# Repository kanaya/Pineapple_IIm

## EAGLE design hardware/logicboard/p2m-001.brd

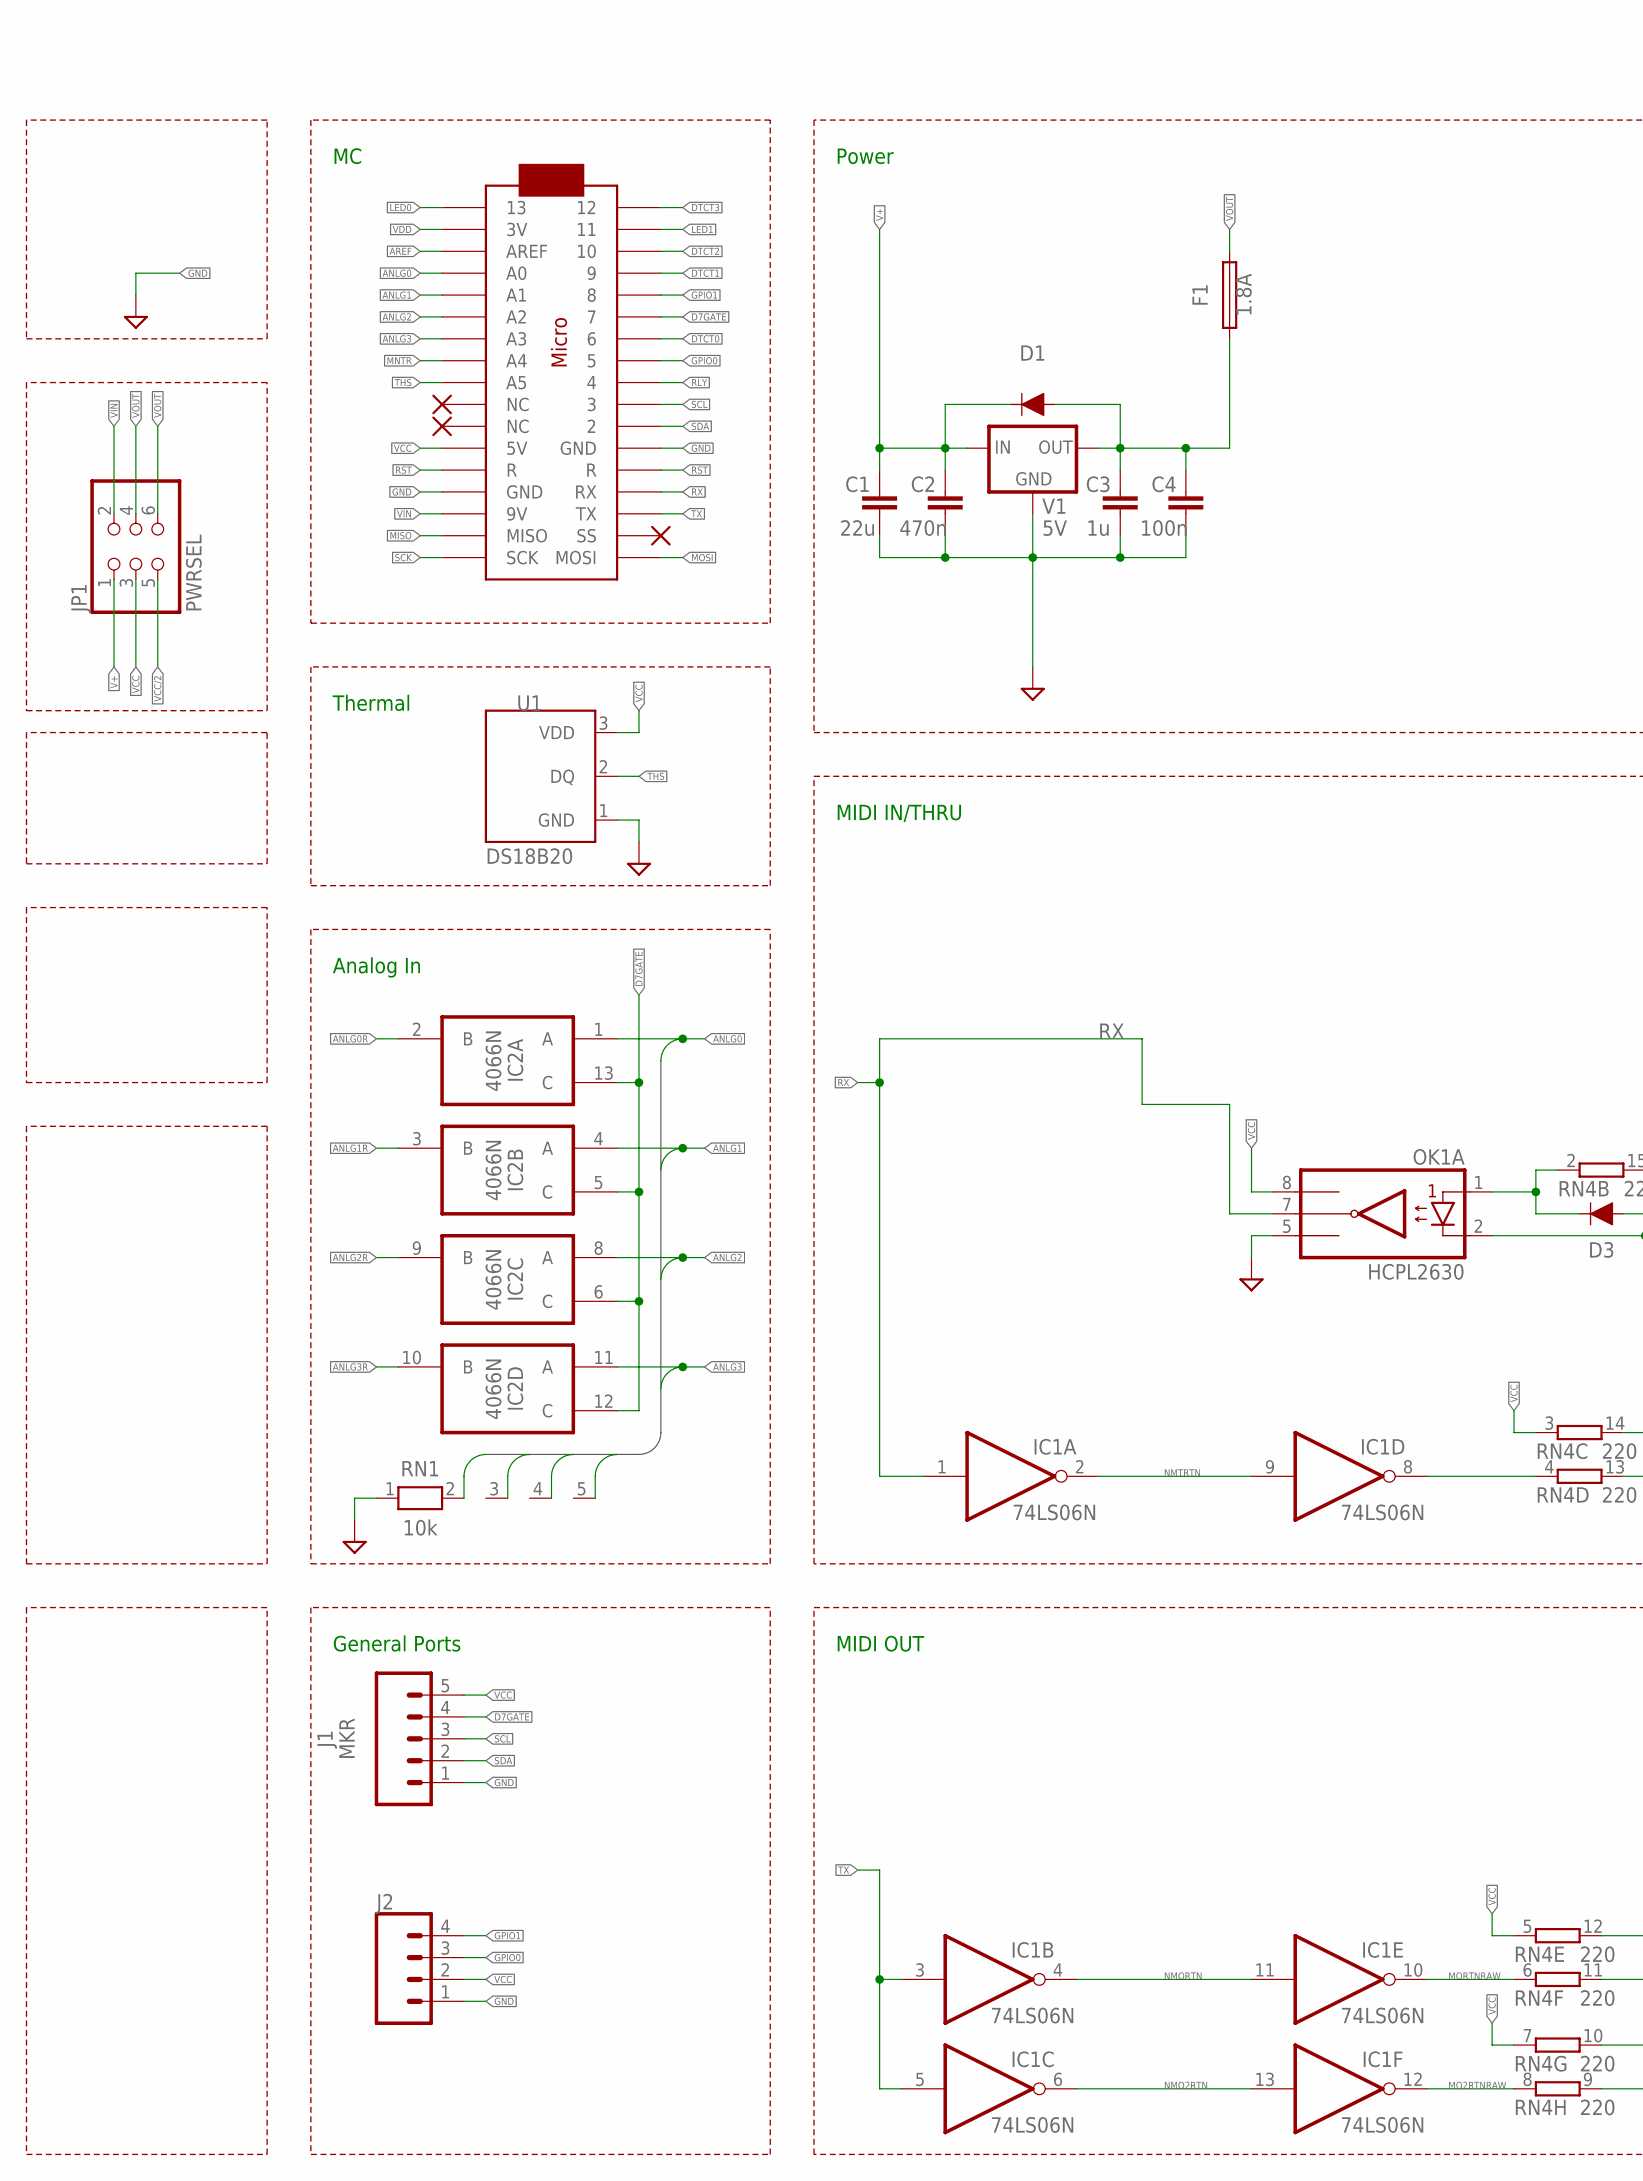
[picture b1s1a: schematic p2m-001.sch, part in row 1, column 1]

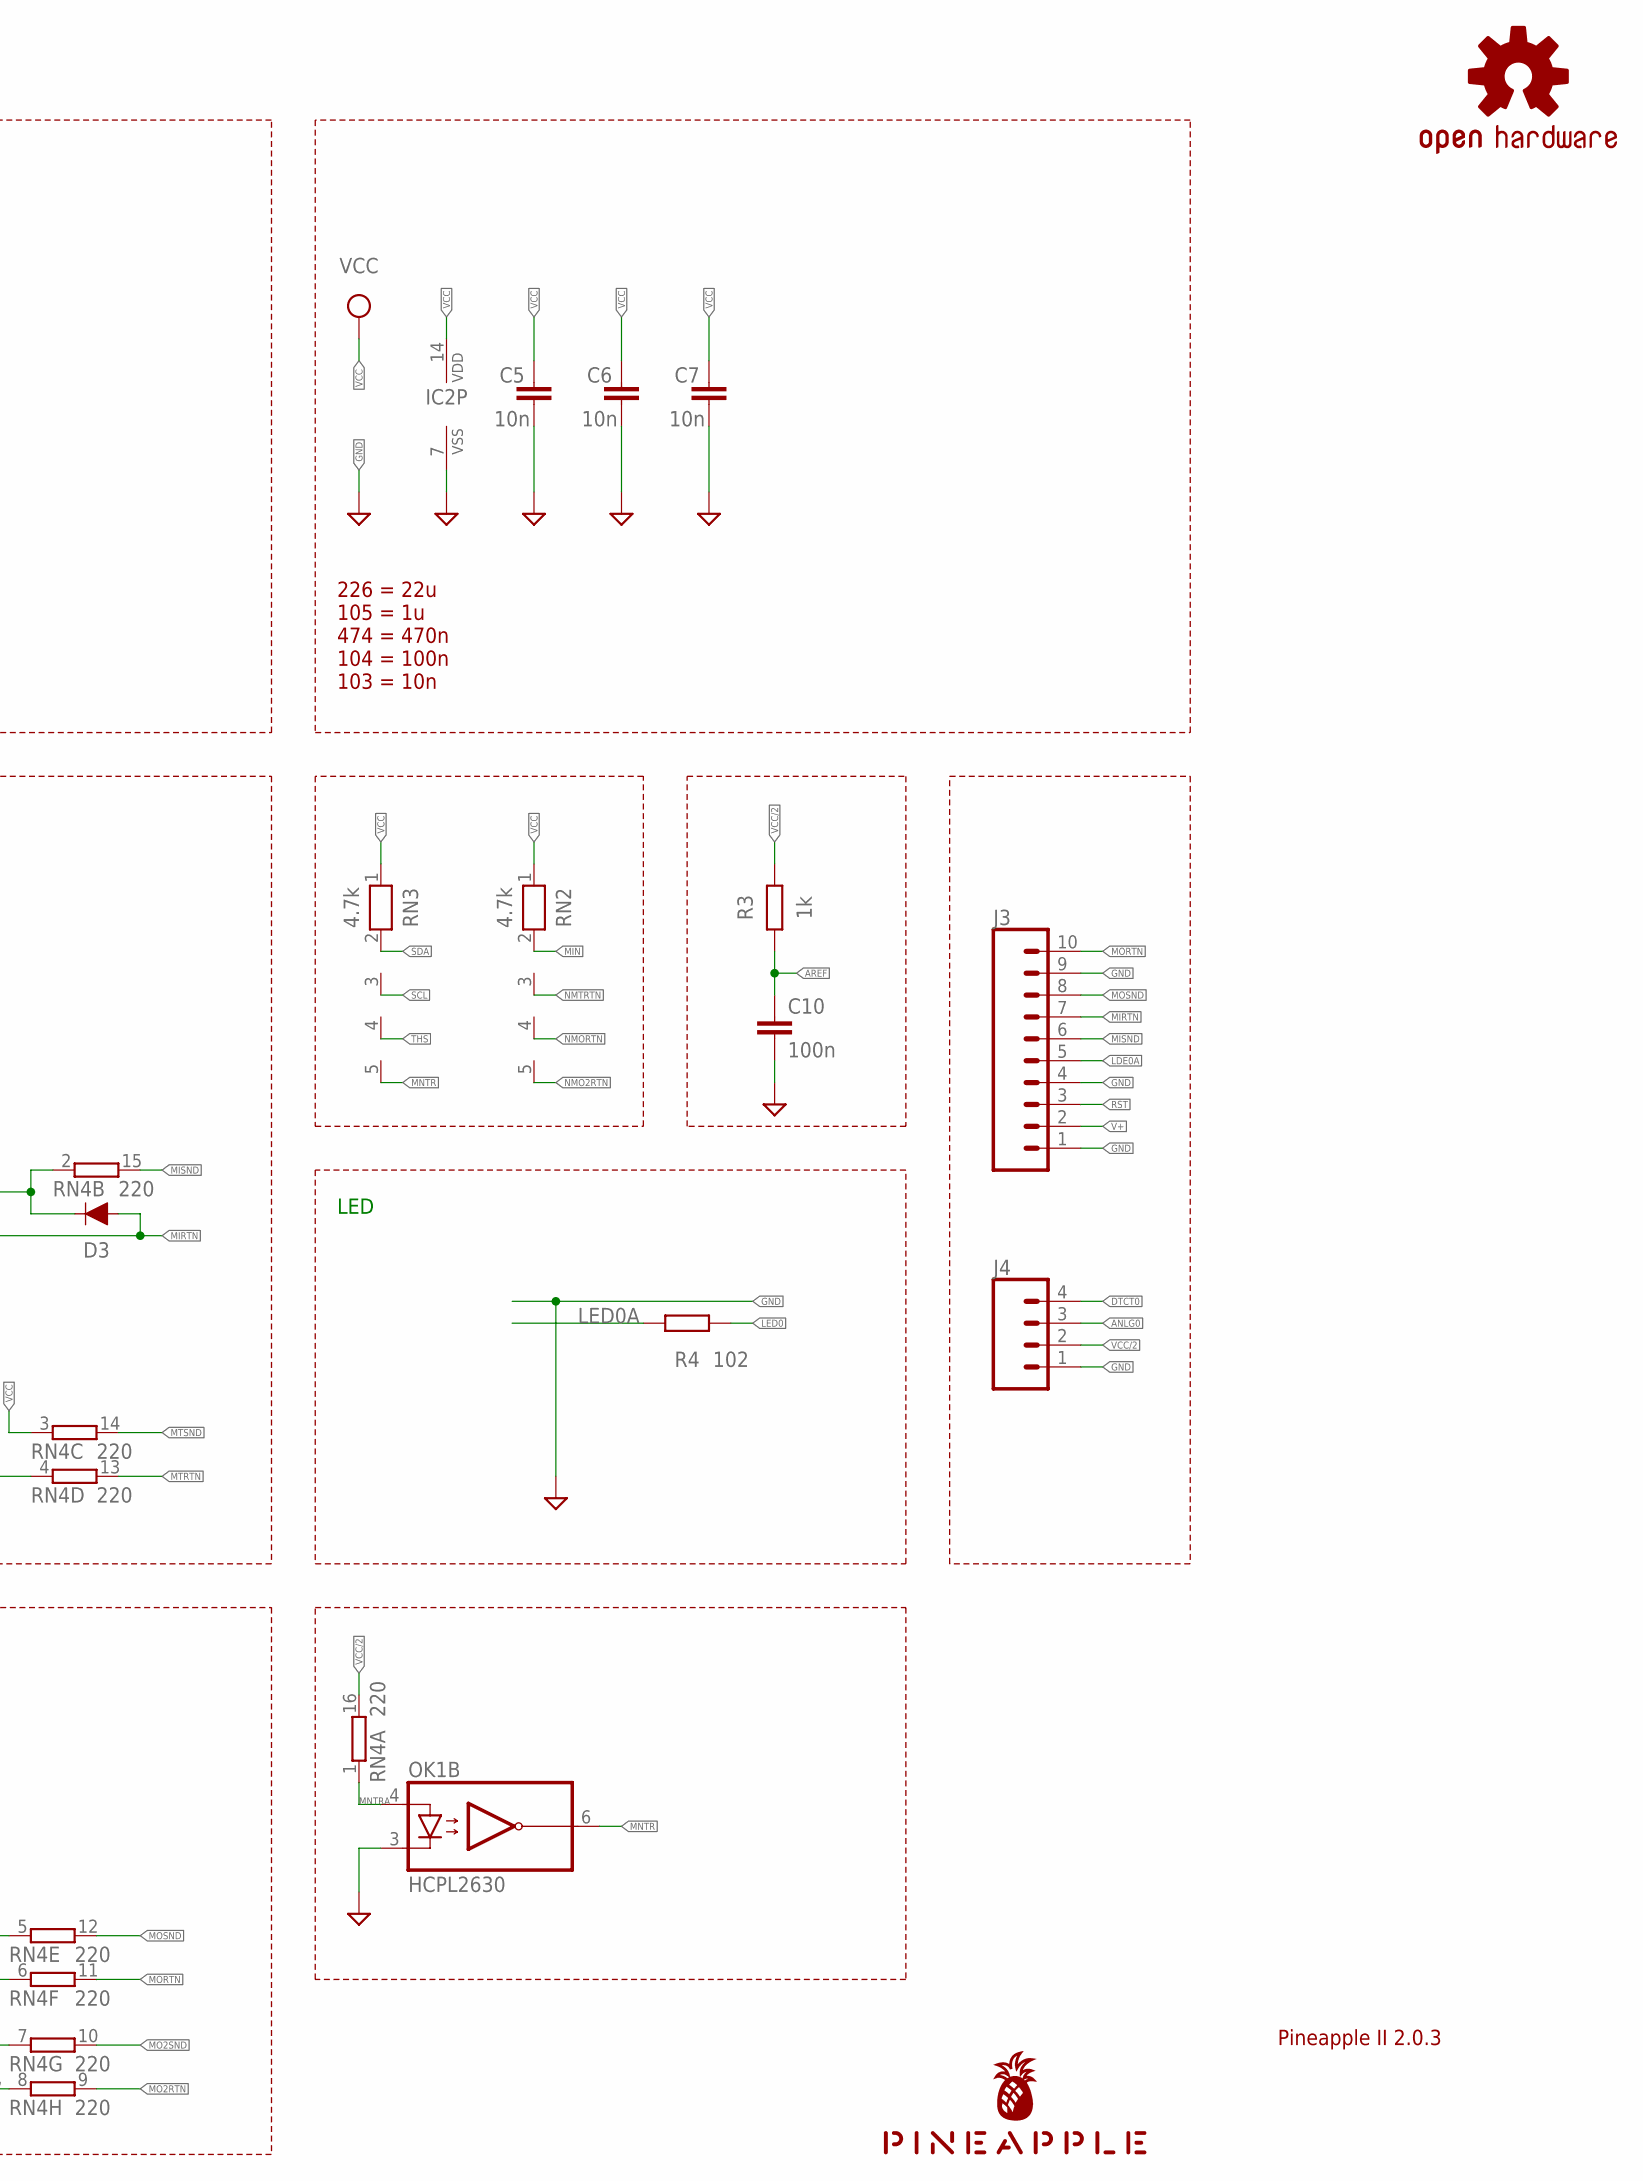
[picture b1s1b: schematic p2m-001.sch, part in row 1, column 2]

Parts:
C1: 22u; C025-050X050
C2: 470n; C050-024X044
C3: 1u; C050-024X044
C4, C10: 100n; C025-024X044
C5, C6, C7: 10n; C025-024X044
D1, D3: DIODE-1N4148
F1: 1.8A; TE5
IC1: 74LS06N; DIL14
IC2: 4066N; DIL14
J1: MKR; JST-5-PTH
J2, J4: CONN_04JST-PTH; JST-4-PTH
J3: CONN_102MM; 1X10-2MM
JP1: PWRSEL; 2X03
LOGO1: OSHW-LOGOS-COPPER; OSHW-LOGO-S_COPPER
MC1: ARDUINOMICRO
OK1: HCPL2630; DIL08
R3: 1k; 0204/5
R4: 102; 0204/5
RN1: 10k; RN-5
RN2, RN3: 4.7k; RN-5
RN4: 220; DIL16
U1: DS18B20; TO-92-AMMO
U$1: PINEAPPLE450_SILK
V1: 5V; 78XXL

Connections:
ANLG0: IC2.1 (A), J4.3, MC1.P$31 (A0), RN1.2
ANLG0R: IC2.2 (B)
ANLG1: IC2.4 (A), MC1.P$30 (A1), RN1.3
ANLG1R: IC2.3 (B)
ANLG2: IC2.8 (A), MC1.P$29 (A2), RN1.4
ANLG2R: IC2.9 (B)
ANLG3: IC2.11 (A), MC1.P$28 (A3), RN1.5
ANLG3R: IC2.10 (B)
AREF: C10.1, MC1.P$32 (AREF), R3.1
D7GATE: IC2.5 (C), IC2.6 (C), IC2.12 (C), IC2.13 (C), J1.4, MC1.P$6 (7)
DTCT0: J4.4, MC1.P$7 (6)
DTCT1: MC1.P$4 (9)
DTCT2: MC1.P$3 (10)
DTCT3: MC1.P$1 (12)
GND: C1.2, C2.2, C3.2, C4.2, C5.2, C6.2, C7.2, C10.2, IC1.7 (GND), IC2.7 (VSS), J1.1, J2.1, J3.1, J3.4, J3.9, J4.1, MC1.P$12 (GND), MC1.P$21 (GND), OK1.3 (C2), OK1.5 (GND), RN1.1, U1.1 (GND), V1.GND
GPIO0: J2.3, MC1.P$8 (5)
GPIO1: J2.4, MC1.P$5 (8)
LDE0A: J3.5
LED0: MC1.P$34 (13), R4.2
LED0A: R4.1
LED1: MC1.P$2 (11)
MIDIINSND: D3.C, OK1.1 (A1), RN4.2 (1)
MIN: RN2.2
MIRTN: D3.A, J3.7, OK1.2 (C1)
MISND: J3.6, RN4.15 (2)
MISO: MC1.P$19 (MISO)
MNTR: MC1.P$27 (A4), OK1.6 (VO2), RN3.5
MNTRA: OK1.4 (A2), RN4.1
MO2RTN: RN4.9 (2)
MO2RTNRAW: IC1.12 (O), RN4.8 (1)
MO2SND: RN4.10 (2)
MORTN: J3.10, RN4.11 (2)
MORTNRAW: IC1.10 (O), RN4.6 (1)
MOSI: MC1.P$17 (MOSI)
MOSND: J3.8, RN4.12 (2)
MTRTN: RN4.13 (2)
MTRTNRAW: IC1.8 (O), RN4.4 (1)
MTSND: RN4.14 (2)
NMO2RTN: IC1.6 (O), IC1.13 (I), RN2.5
NMORTN: IC1.4 (O), IC1.11 (I), RN2.4
NMTRTN: IC1.2 (O), IC1.9 (I), RN2.3
RLY: MC1.P$9 (4)
RST: J3.3, MC1.P$13 (R), MC1.P$22 (R)
RX: IC1.1 (I), MC1.P$14 (RX), OK1.7 (VO1)
SCK: MC1.P$18 (SCK)
SCL: J1.3, MC1.P$10 (3), RN3.3
SDA: J1.2, MC1.P$11 (2), RN3.2
THS: MC1.P$26 (A5), RN3.4, U1.2 (DQ)
TX: IC1.3 (I), IC1.5 (I), MC1.P$15 (TX)
V+: C1.1, C2.1, D1.C, J3.2, JP1.1, V1.IN
VCC: C5.1, C6.1, C7.1, IC1.14 (VCC), IC2.14 (VDD), J1.5, J2.2, JP1.3, MC1.P$23 (5V), OK1.8 (VCC), RN2.1, RN3.1, RN4.3 (1), RN4.5 (1), RN4.7 (1), U1.3 (VDD)
VCC/2: J4.2, JP1.5, R3.2, RN4.16 (2)
VDD: MC1.P$33 (3V)
VIN: JP1.2, MC1.P$20 (9V)
VOUT: F1.2, JP1.4, JP1.6
VOUTRAW: C3.1, C4.1, D1.A, F1.1, V1.OUT

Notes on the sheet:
Pineapple II 2.0.3
226 = 22u 105 = 1u 474 = 470n 104 = 100n 103 = 10n
MIDI IN/THRU
MIDI OUT
Power
General Ports
Analog In
Thermal
LED

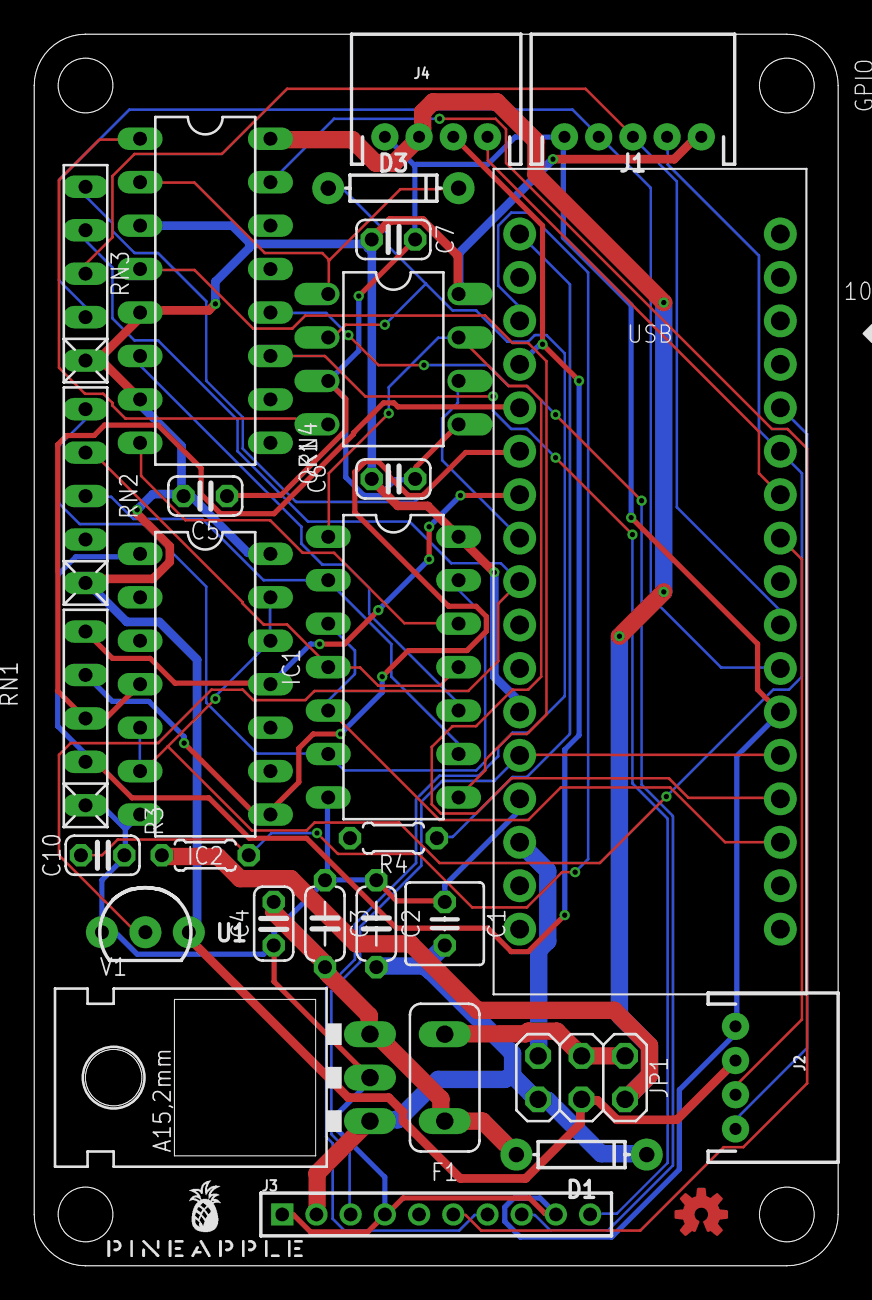
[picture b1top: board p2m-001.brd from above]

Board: 2 copper layers, 47.0 x 72.0 mm, 30 parts (0 on the bottom side), 36 nets.

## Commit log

2022-11-10 Imported schematic and artwork from Pineapple II 2.7 support branch.
2022-11-10 First try.
2022-11-10 Second try.

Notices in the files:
parts and their libraries:
SparkFun-DiscreteSemi: Licensing: Creative Commons ShareAlike 4.0 International - https://creativecommons.org/licenses/by-sa/4.0
